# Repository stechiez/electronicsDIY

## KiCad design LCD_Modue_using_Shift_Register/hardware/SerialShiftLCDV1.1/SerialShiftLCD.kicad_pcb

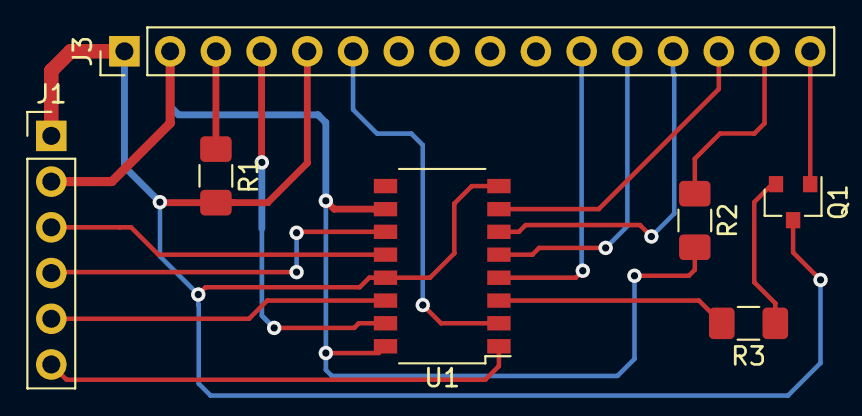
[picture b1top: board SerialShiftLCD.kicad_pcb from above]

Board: 2 copper layers, 7 parts (0 on the bottom side), 17 nets.

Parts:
J1: Conn_01x06; PinHeader_1x06_P2.54mm_Vertical
J3: Conn_01x16; PinHeader_1x16_P2.54mm_Vertical
Q1: BC547; SOT-23
R1, R2, R3: R; R_1206_3216Metric_Pad1.42x1.75mm_HandSolder
U1: 74HC595; SOP-16_4.4x10.4mm_P1.27mm

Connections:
+5V: J1.2, J3.2, R2.2, U1.10, U1.16
GND: J1.1, J3.1, J3.5, Q1.3, R1.2, U1.8, U1.13
unnamed: J1.3, U1.12
unnamed: J1.4, U1.11
unnamed: J1.5, U1.14
unnamed: J1.6, U1.1
unnamed: J3.3, R1.1
unnamed: J3.4, U1.15
unnamed: J3.6, U1.2
unnamed: J3.11, U1.4
unnamed: J3.12, U1.5
unnamed: J3.13, U1.6
unnamed: J3.14, U1.7
unnamed: J3.15, R2.1
unnamed: J3.16, Q1.1
unnamed: Q1.2, R3.1
unnamed: R3.2, U1.3

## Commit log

2019-10-08 moving files to single repo
2020-01-04 Adding Custom Designed Seven Segment Display
2020-02-05 adding gerber files to repo
2020-10-09 Connection diagram for PIC with Arduino
    Connection diagram for PIC with Arduino for LVP programmer
2021-02-20 LCD Module using shift register
